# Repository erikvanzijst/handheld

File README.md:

# 8-bit handheld multiplayer gaming device

An Open Source Hardware custom designed handheld gaming device.

* powered by an 8-bit AVR XMEGA microcontroller
* ultra low-res 24x16 monochrome display made of discrete LEDS
* authentic 8-bit retro sound and music
* EEPROM-based hiscores
* multiplayer over bidirectional infrared communication
* battery or USB powered

Project write-up at: https://medium.com/@erikvanzijst/diy-8-bit-handheld-multiplayer-gaming-device-cc30baae7372

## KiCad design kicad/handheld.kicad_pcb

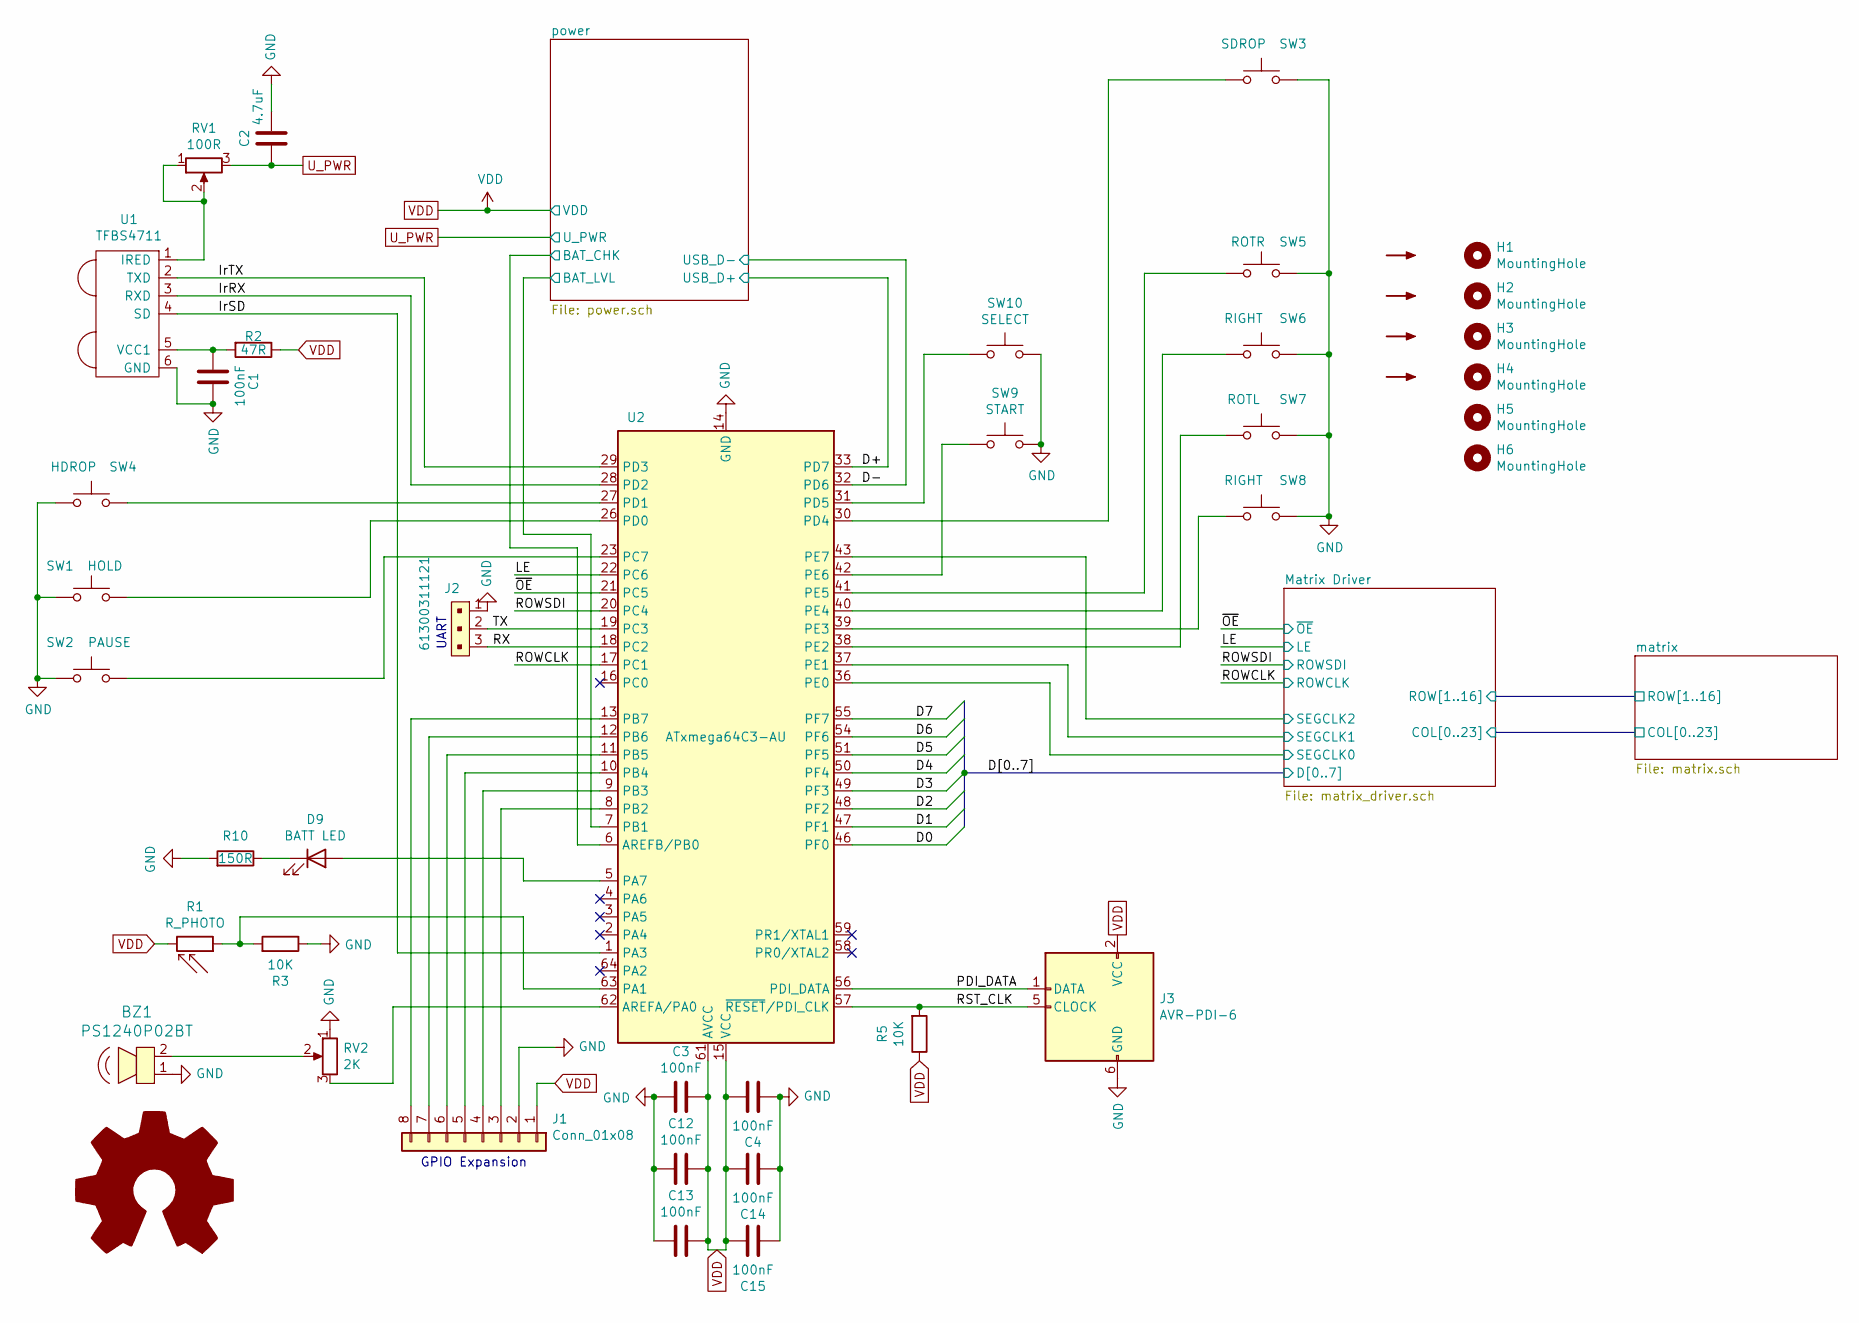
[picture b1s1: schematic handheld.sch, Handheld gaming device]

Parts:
BZ1: PS1240P02BT; Piezo_Transducer_THT_PS1240P02BT; MPN PS1240P02BT; Digi-Key_PN 445-2525-1-ND
C1, C3, C4, C12, C13, C14, C15: 100nF; C_0805_2012Metric_Pad1.15x1.40mm_HandSolder
C2: 4.7uF; C_0805_2012Metric_Pad1.15x1.40mm_HandSolder
D9: BATT LED; LED_D3.0mm
H1, H2, H3, H4, H5, H6: MountingHole; MountingHole_3.2mm_M3
J1: Conn_01x08; PinSocket_1x08_P2.54mm_Horizontal
J2: 61300311121; PinSocket_1x03_P2.54mm_Horizontal; MPN 61300311121; Digi-Key_PN 732-5316-ND
J3: AVR-PDI-6; AVR_PDI_Header_2x03_P2.54mm_Vertical
R1: R_PHOTO; R_LDR_5.1x4.3mm_P3.4mm_Vertical
R2: 47R; R_0805_2012Metric_Pad1.15x1.40mm_HandSolder
R3, R5: 10K; R_0805_2012Metric_Pad1.15x1.40mm_HandSolder
R10: 150R; R_0805_2012Metric_Pad1.15x1.40mm_HandSolder
RV1: 100R; Potentiometer_Bourns_TC33X_Vertical
RV2: 2K; Potentiometer_Bourns_TC33X_Vertical
SW1: HOLD; SW_PUSH-12mm
SW2: PAUSE; SW_PUSH-12mm
SW3: SDROP; SW_PUSH-12mm
SW4: HDROP; SW_PUSH-12mm
SW5: ROTR; SW_PUSH-12mm
SW6, SW8: RIGHT; SW_PUSH-12mm
SW7: ROTL; SW_PUSH-12mm
SW9: START; SW_PUSH_6mm
SW10: SELECT; SW_PUSH_6mm
U1: TFBS4711; TFBS4711-IrDA
U2: ATxmega64C3-AU; TQFP-64_14x14mm_P0.8mm

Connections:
/D0: U2.46 (PF0); also elsewhere on the board
/D1: U2.47 (PF1); also elsewhere on the board
/D2: U2.48 (PF2); also elsewhere on the board
/D3: U2.49 (PF3); also elsewhere on the board
/D4: U2.50 (PF4); also elsewhere on the board
/D5: U2.51 (PF5); also elsewhere on the board
/D6: U2.54 (PF6); also elsewhere on the board
/D7: U2.55 (PF7); also elsewhere on the board
/D+: U2.33 (PD7); also elsewhere on the board
/D-: U2.32 (PD6); also elsewhere on the board
/IrRX: U1.3 (RXD), U2.28 (PD2)
/IrSD: U1.4 (SD), U2.1 (PA3)
/IrTX: U1.2 (TXD), U2.29 (PD3)
/LE: U2.22 (PC6); also elsewhere on the board
/Matrix Driver/SEGCLK0: U2.36 (PE0); also elsewhere on the board
/Matrix Driver/SEGCLK1: U2.37 (PE1); also elsewhere on the board
/Matrix Driver/SEGCLK2: U2.43 (PE7); also elsewhere on the board
/PDI_DATA: J3.1 (DATA), U2.56 (PDI_DATA)
/ROWCLK: U2.17 (PC1); also elsewhere on the board
/ROWSDI: U2.20 (PC4); also elsewhere on the board
/RST_CLK: J3.5 (CLOCK), R5.2, U2.57 (~RESET~/PDI_CLK)
/RX: J2.3, U2.18 (PC2)
/TX: J2.2, U2.19 (PC3)
/power/BAT_CHK: U2.6 (AREFB/PB0); also elsewhere on the board
/power/BAT_LVL: U2.7 (PB1); also elsewhere on the board
/~OE: U2.21 (PC5); also elsewhere on the board
GND: BZ1.1, C1.1, C2.2, C3.2, C4.2, C12.2, C13.2, C14.2, C15.2, J1.2, J2.1, J3.6 (GND), R3.1, R10.2, RV2.1, SW1.1, SW2.1, SW3.1, SW4.2, SW5.1, SW6.1, SW7.1, SW8.1, SW9.2, SW10.2, U1.6 (GND), U2.14 (GND), U2.24 (GND), U2.34 (GND), U2.44 (GND), U2.52 (GND), U2.60 (GND); also elsewhere on the board
unnamed: BZ1.2, RV2.2
unnamed: C1.2, R2.2, U1.5 (VCC1)
unnamed: D9.1 (K), R10.1
unnamed: D9.2 (A), U2.5 (PA7)
unnamed: J1.3, U2.8 (PB2)
unnamed: J1.4, U2.9 (PB3)
unnamed: J1.5, U2.10 (PB4)
unnamed: J1.6, U2.11 (PB5)
unnamed: J1.7, U2.12 (PB6)
unnamed: J1.8, U2.13 (PB7)
unnamed: R1.1, R3.2, U2.63 (PA1)
unnamed: RV1.1, RV1.2, U1.1 (IRED)
unnamed: RV2.3, U2.62 (AREFA/PA0)
unnamed: SW1.2, U2.26 (PD0)
unnamed: SW2.2, U2.23 (PC7)
unnamed: SW3.2, U2.30 (PD4)
unnamed: SW4.1, U2.27 (PD1)
unnamed: SW5.2, U2.41 (PE5)
unnamed: SW6.2, U2.40 (PE4)
unnamed: SW7.2, U2.38 (PE2)
unnamed: SW8.2, U2.39 (PE3)
unnamed: SW9.1, U2.42 (PE6)
unnamed: SW10.1, U2.31 (PD5)
U_PWR: C2.1, RV1.3; also elsewhere on the board
VDD: C3.1, C4.1, C12.1, C13.1, C14.1, C15.1, J1.1, J3.2 (VCC), R1.2, R2.1, R5.1, U2.15 (VCC), U2.25 (VCC), U2.35 (VCC), U2.45 (VCC), U2.53 (VCC), U2.61 (AVCC); also elsewhere on the board

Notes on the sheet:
UART
GPIO Expansion

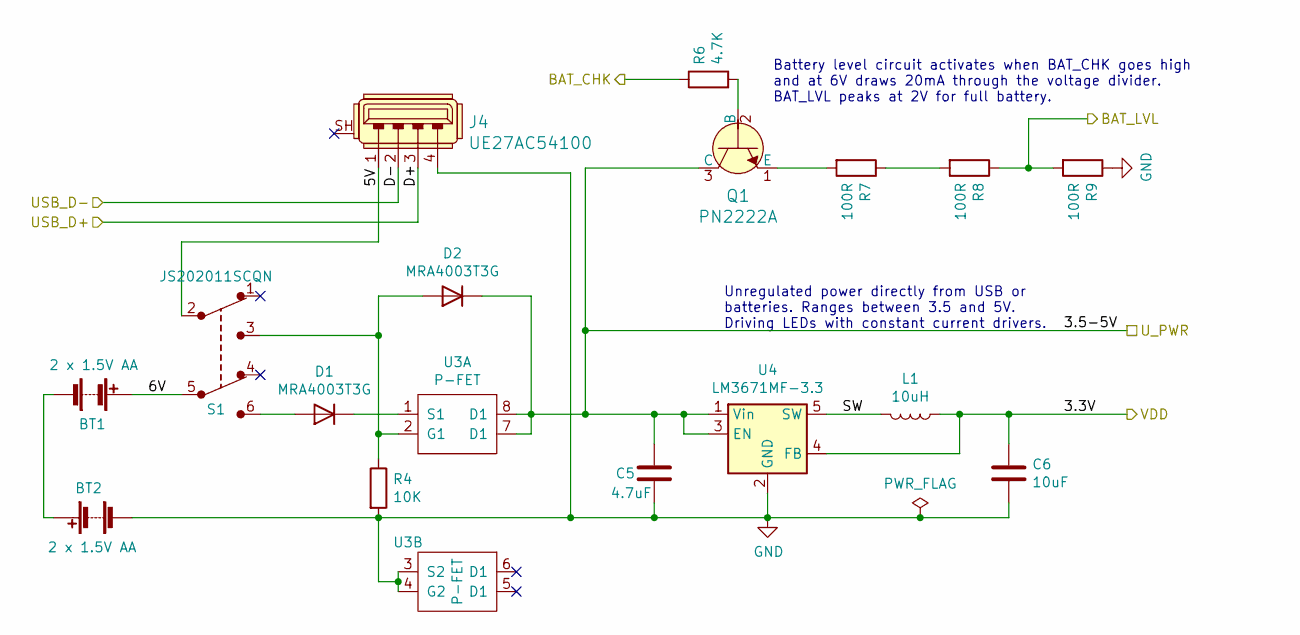
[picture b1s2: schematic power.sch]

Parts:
BT1, BT2: 2 x 1.5V AA; BatteryHolder_MPD_BC12AAPC_2xAA
C5: 4.7uF; C_0805_2012Metric_Pad1.15x1.40mm_HandSolder
C6: 10uF; C_0805_2012Metric_Pad1.15x1.40mm_HandSolder
D1, D2: MRA4003T3G; D_SMA
J4: UE27AC54100; USB_A_Female_UE27AC54100; MPN UE27AC54100; Digi-Key_PN UE27AC54100-ND
L1: 10uH; CDRH5D18NP
Q1: PN2222A; TO-92_Inline_W4.0mm_Horizontal_FlatSideDown; MPN PN2222A; Digi-Key_PN PN2222ACS-ND
R4: 10K; R_0805_2012Metric_Pad1.15x1.40mm_HandSolder
R6: 4.7K; R_0805_2012Metric_Pad1.15x1.40mm_HandSolder
R7, R8, R9: 100R; R_0805_2012Metric_Pad1.15x1.40mm_HandSolder
S1: JS202011SCQN; SW_CuK_JS202011AQN_DPDT_Angled; MPN JS202011SCQN; Digi-Key_PN 401-2002-1-ND
U3: P-FET; SOIC-8_3.9x4.9mm_P1.27mm
U4: LM3671MF-3.3; TSOT-23-5

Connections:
/D+: J4.3; also elsewhere on the board
/D-: J4.2; also elsewhere on the board
/power/5V: J4.1, S1.2
/power/6V: BT1.1 (+), S1.5
/power/BAT_CHK: R6.1; also elsewhere on the board
/power/BAT_LVL: R8.1, R9.2; also elsewhere on the board
/power/SW: L1.2, U4.5 (SW)
GND: BT2.2 (-), C5.2, C6.2, J4.4, R4.2, R9.1, U3.3 (S2), U3.4 (G2), U4.2 (GND); also elsewhere on the board
unnamed: BT1.2 (-), BT2.1 (+)
unnamed: D1.1 (K), U3.1 (S1)
unnamed: D1.2 (A), S1.6
unnamed: D2.2 (A), R4.1, S1.3, U3.2 (G1)
unnamed: Q1.1 (E), R7.2
unnamed: Q1.2 (B), R6.2
unnamed: R7.1, R8.2
U_PWR: C5.1, D2.1 (K), Q1.3 (C), U3.7 (D1), U3.8 (D1), U4.1 (Vin), U4.3 (EN); also elsewhere on the board
VDD: C6.1, L1.1, U4.4 (FB); also elsewhere on the board

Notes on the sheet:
Unregulated power directly from USB or batteries. Ranges between 3.5 and 5V. Driving LEDs with constant current drivers.
Battery level circuit activates when BAT_CHK goes high and at 6V draws 20mA through the voltage divider. BAT_LVL peaks at 2V for full battery.

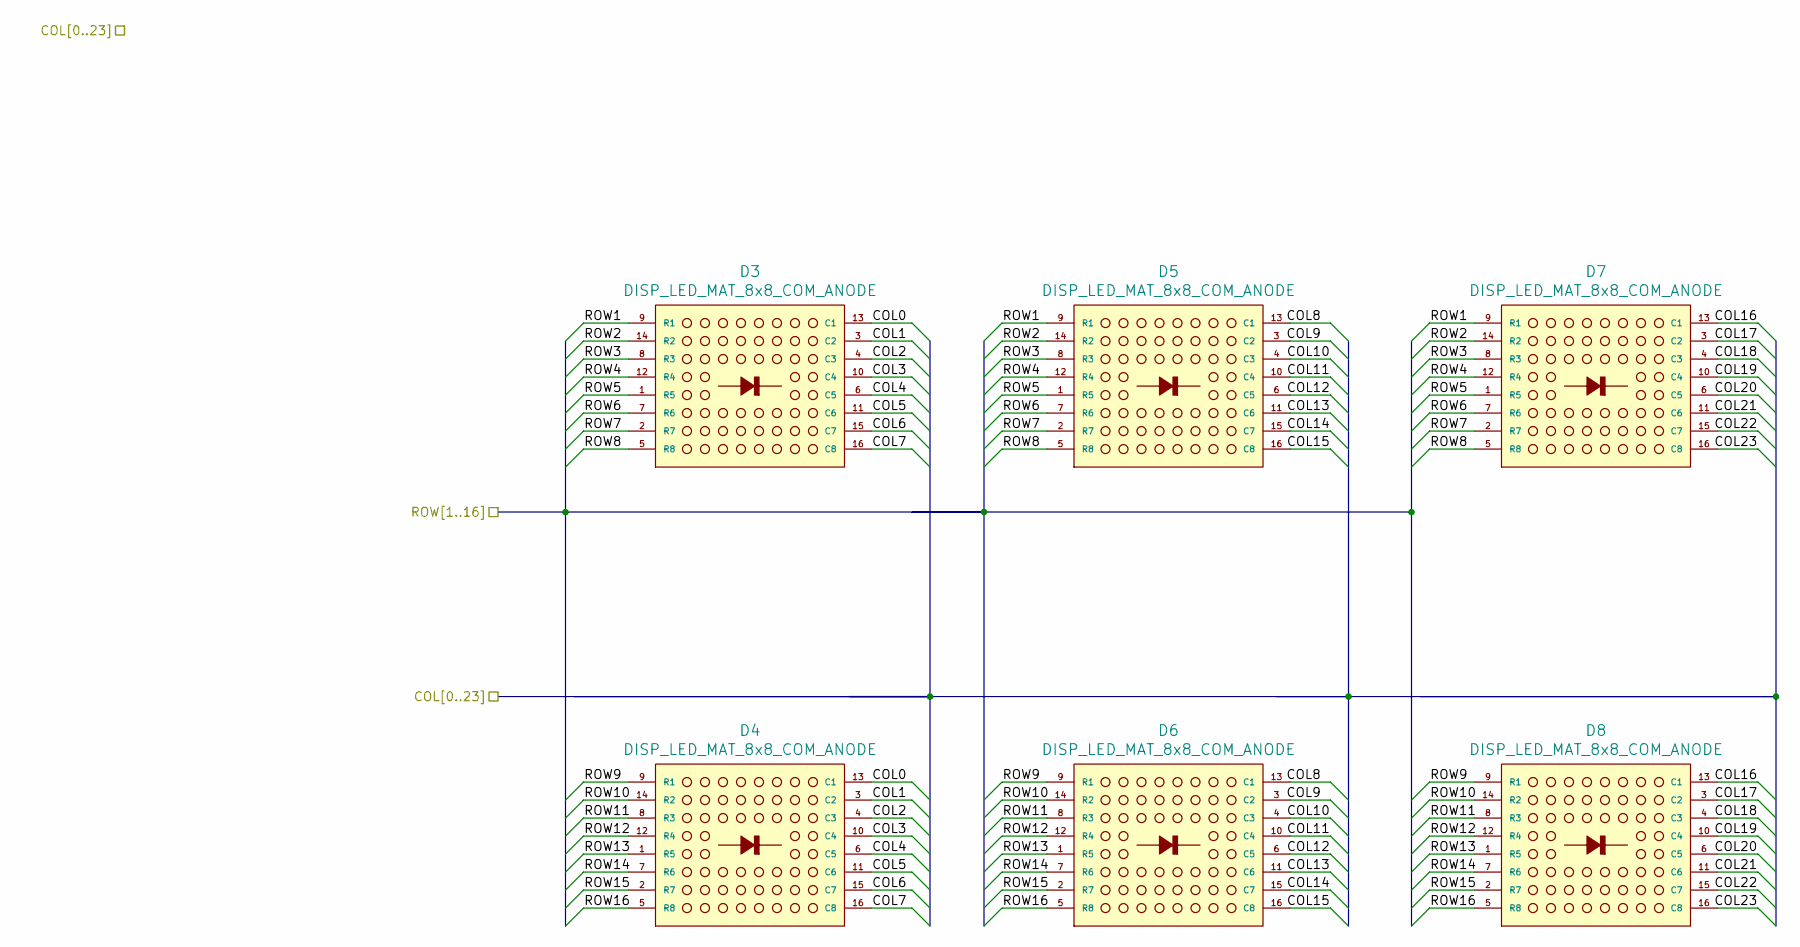
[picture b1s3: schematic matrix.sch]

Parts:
D3, D4, D5, D6, D7, D8: DISP_LED_MAT_8x8_COM_ANODE; LED_8x8_3MM_38x38MM

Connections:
/Matrix Driver/COL0: D3.13 (C1), D4.13 (C1); also elsewhere on the board
/Matrix Driver/COL1: D3.3 (C2), D4.3 (C2); also elsewhere on the board
/Matrix Driver/COL2: D3.4 (C3), D4.4 (C3); also elsewhere on the board
/Matrix Driver/COL3: D3.10 (C4), D4.10 (C4); also elsewhere on the board
/Matrix Driver/COL4: D3.6 (C5), D4.6 (C5); also elsewhere on the board
/Matrix Driver/COL5: D3.11 (C6), D4.11 (C6); also elsewhere on the board
/Matrix Driver/COL6: D3.15 (C7), D4.15 (C7); also elsewhere on the board
/Matrix Driver/COL7: D3.16 (C8), D4.16 (C8); also elsewhere on the board
/Matrix Driver/COL8: D5.13 (C1), D6.13 (C1); also elsewhere on the board
/Matrix Driver/COL9: D5.3 (C2), D6.3 (C2); also elsewhere on the board
/Matrix Driver/COL10: D5.4 (C3), D6.4 (C3); also elsewhere on the board
/Matrix Driver/COL11: D5.10 (C4), D6.10 (C4); also elsewhere on the board
/Matrix Driver/COL12: D5.6 (C5), D6.6 (C5); also elsewhere on the board
/Matrix Driver/COL13: D5.11 (C6), D6.11 (C6); also elsewhere on the board
/Matrix Driver/COL14: D5.15 (C7), D6.15 (C7); also elsewhere on the board
/Matrix Driver/COL15: D5.16 (C8), D6.16 (C8); also elsewhere on the board
/Matrix Driver/COL16: D7.13 (C1), D8.13 (C1); also elsewhere on the board
/Matrix Driver/COL17: D7.3 (C2), D8.3 (C2); also elsewhere on the board
/Matrix Driver/COL18: D7.4 (C3), D8.4 (C3); also elsewhere on the board
/Matrix Driver/COL19: D7.10 (C4), D8.10 (C4); also elsewhere on the board
/Matrix Driver/COL20: D7.6 (C5), D8.6 (C5); also elsewhere on the board
/Matrix Driver/COL21: D7.11 (C6), D8.11 (C6); also elsewhere on the board
/Matrix Driver/COL22: D7.15 (C7), D8.15 (C7); also elsewhere on the board
/Matrix Driver/COL23: D7.16 (C8), D8.16 (C8); also elsewhere on the board
/Matrix Driver/ROW1: D3.9 (R1), D5.9 (R1), D7.9 (R1); also elsewhere on the board
/Matrix Driver/ROW2: D3.14 (R2), D5.14 (R2), D7.14 (R2); also elsewhere on the board
/Matrix Driver/ROW3: D3.8 (R3), D5.8 (R3), D7.8 (R3); also elsewhere on the board
/Matrix Driver/ROW4: D3.12 (R4), D5.12 (R4), D7.12 (R4); also elsewhere on the board
/Matrix Driver/ROW5: D3.1 (R5), D5.1 (R5), D7.1 (R5); also elsewhere on the board
/Matrix Driver/ROW6: D3.7 (R6), D5.7 (R6), D7.7 (R6); also elsewhere on the board
/Matrix Driver/ROW7: D3.2 (R7), D5.2 (R7), D7.2 (R7); also elsewhere on the board
/Matrix Driver/ROW8: D3.5 (R8), D5.5 (R8), D7.5 (R8); also elsewhere on the board
/Matrix Driver/ROW9: D4.9 (R1), D6.9 (R1), D8.9 (R1); also elsewhere on the board
/Matrix Driver/ROW10: D4.14 (R2), D6.14 (R2), D8.14 (R2); also elsewhere on the board
/Matrix Driver/ROW11: D4.8 (R3), D6.8 (R3), D8.8 (R3); also elsewhere on the board
/Matrix Driver/ROW12: D4.12 (R4), D6.12 (R4), D8.12 (R4); also elsewhere on the board
/Matrix Driver/ROW13: D4.1 (R5), D6.1 (R5), D8.1 (R5); also elsewhere on the board
/Matrix Driver/ROW14: D4.7 (R6), D6.7 (R6), D8.7 (R6); also elsewhere on the board
/Matrix Driver/ROW15: D4.2 (R7), D6.2 (R7), D8.2 (R7); also elsewhere on the board
/Matrix Driver/ROW16: D4.5 (R8), D6.5 (R8), D8.5 (R8); also elsewhere on the board

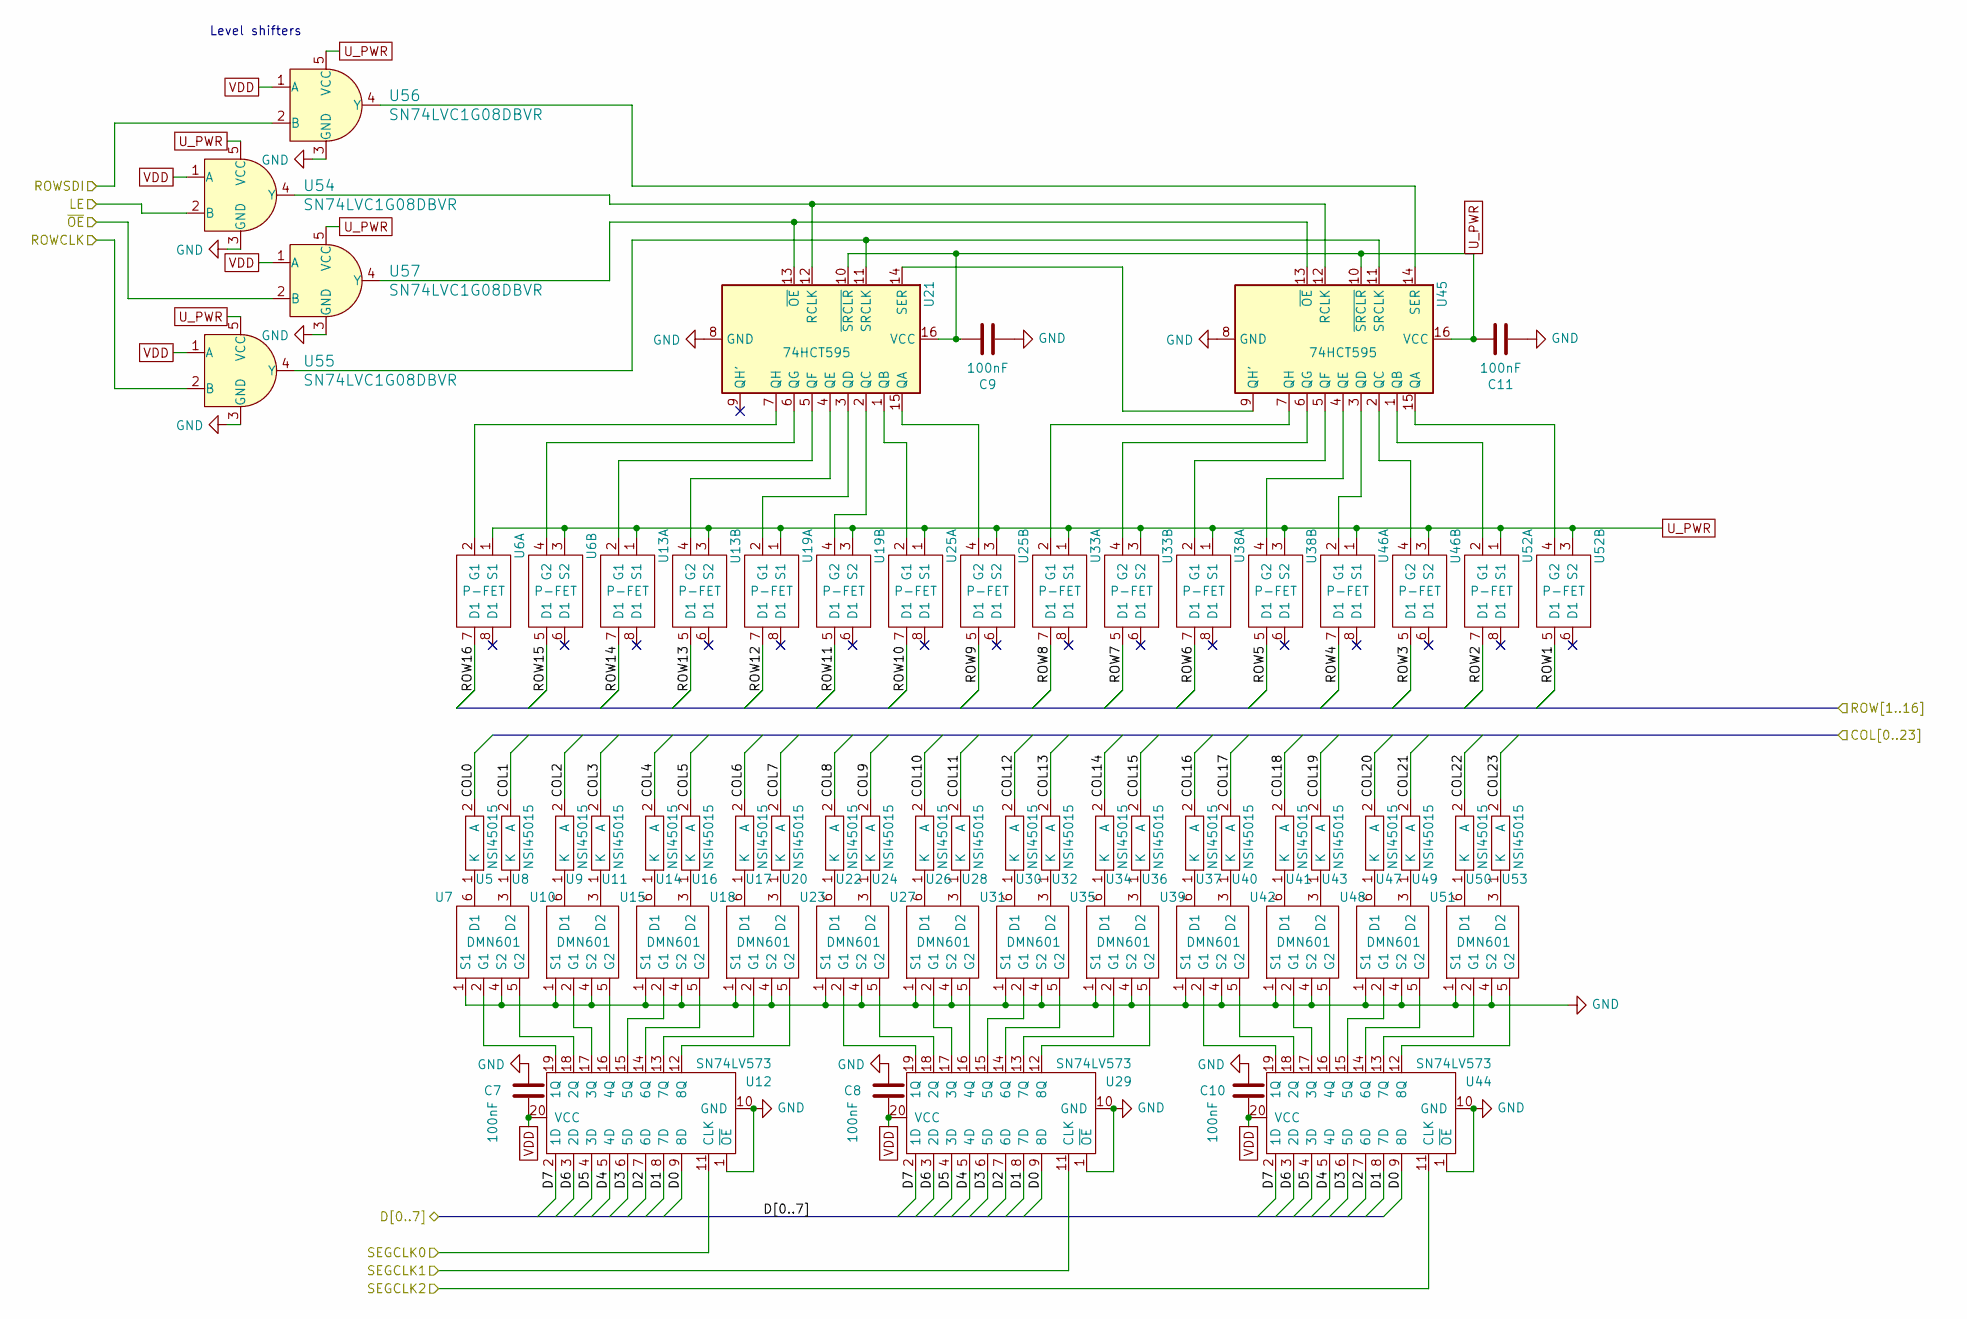
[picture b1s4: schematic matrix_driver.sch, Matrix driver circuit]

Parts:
C7, C8, C9, C10, C11: 100nF; C_0805_2012Metric_Pad1.15x1.40mm_HandSolder
U5, U8, U9, U11, U14, U16, U17, U20, U22, U24, U26, U28, U30, U32, U34, U36, U37, U40, U41, U43, U47, U49, U50, U53: NSI45015; D_SOD-123
U6, U13, U19, U25, U33, U38, U46, U52: P-FET; SOIC-8_3.9x4.9mm_P1.27mm
U7, U10, U15, U18, U23, U27, U31, U35, U39, U42, U48, U51: DMN601; SOT-23-6_Handsoldering
U12, U29, U44: SN74LV573; SO-20_5.3x12.6mm_P1.27mm
U21, U45: 74HCT595; SOIC-16_3.9x9.9mm_P1.27mm
U54, U55, U56, U57: SN74LVC1G08DBVR; SOT-23-5; MPN SN74LVC1G08DBVR; Digi-Key_PN 296-11601-1-ND

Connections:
/D0: U12.9 (8D), U29.9 (8D), U44.9 (8D); also elsewhere on the board
/D1: U12.8 (7D), U29.8 (7D), U44.8 (7D); also elsewhere on the board
/D2: U12.7 (6D), U29.7 (6D), U44.7 (6D); also elsewhere on the board
/D3: U12.6 (5D), U29.6 (5D), U44.6 (5D); also elsewhere on the board
/D4: U12.5 (4D), U29.5 (4D), U44.5 (4D); also elsewhere on the board
/D5: U12.4 (3D), U29.4 (3D), U44.4 (3D); also elsewhere on the board
/D6: U12.3 (2D), U29.3 (2D), U44.3 (2D); also elsewhere on the board
/D7: U12.2 (1D), U29.2 (1D), U44.2 (1D); also elsewhere on the board
/LE: U54.2 (B); also elsewhere on the board
/Matrix Driver/COL0: U5.2 (A); also elsewhere on the board
/Matrix Driver/COL1: U8.2 (A); also elsewhere on the board
/Matrix Driver/COL2: U9.2 (A); also elsewhere on the board
/Matrix Driver/COL3: U11.2 (A); also elsewhere on the board
/Matrix Driver/COL4: U14.2 (A); also elsewhere on the board
/Matrix Driver/COL5: U16.2 (A); also elsewhere on the board
/Matrix Driver/COL6: U17.2 (A); also elsewhere on the board
/Matrix Driver/COL7: U20.2 (A); also elsewhere on the board
/Matrix Driver/COL8: U22.2 (A); also elsewhere on the board
/Matrix Driver/COL9: U24.2 (A); also elsewhere on the board
/Matrix Driver/COL10: U26.2 (A); also elsewhere on the board
/Matrix Driver/COL11: U28.2 (A); also elsewhere on the board
/Matrix Driver/COL12: U30.2 (A); also elsewhere on the board
/Matrix Driver/COL13: U32.2 (A); also elsewhere on the board
/Matrix Driver/COL14: U34.2 (A); also elsewhere on the board
/Matrix Driver/COL15: U36.2 (A); also elsewhere on the board
/Matrix Driver/COL16: U37.2 (A); also elsewhere on the board
/Matrix Driver/COL17: U40.2 (A); also elsewhere on the board
/Matrix Driver/COL18: U41.2 (A); also elsewhere on the board
/Matrix Driver/COL19: U43.2 (A); also elsewhere on the board
/Matrix Driver/COL20: U47.2 (A); also elsewhere on the board
/Matrix Driver/COL21: U49.2 (A); also elsewhere on the board
/Matrix Driver/COL22: U50.2 (A); also elsewhere on the board
/Matrix Driver/COL23: U53.2 (A); also elsewhere on the board
/Matrix Driver/ROW1: U52.5 (D1); also elsewhere on the board
/Matrix Driver/ROW2: U52.7 (D1); also elsewhere on the board
/Matrix Driver/ROW3: U46.5 (D1); also elsewhere on the board
/Matrix Driver/ROW4: U46.7 (D1); also elsewhere on the board
/Matrix Driver/ROW5: U38.5 (D1); also elsewhere on the board
/Matrix Driver/ROW6: U38.7 (D1); also elsewhere on the board
/Matrix Driver/ROW7: U33.5 (D1); also elsewhere on the board
/Matrix Driver/ROW8: U33.7 (D1); also elsewhere on the board
/Matrix Driver/ROW9: U25.5 (D1); also elsewhere on the board
/Matrix Driver/ROW10: U25.7 (D1); also elsewhere on the board
/Matrix Driver/ROW11: U19.5 (D1); also elsewhere on the board
/Matrix Driver/ROW12: U19.7 (D1); also elsewhere on the board
/Matrix Driver/ROW13: U13.5 (D1); also elsewhere on the board
/Matrix Driver/ROW14: U13.7 (D1); also elsewhere on the board
/Matrix Driver/ROW15: U6.5 (D1); also elsewhere on the board
/Matrix Driver/ROW16: U6.7 (D1); also elsewhere on the board
/Matrix Driver/SEGCLK0: U12.11 (CLK); also elsewhere on the board
/Matrix Driver/SEGCLK1: U29.11 (CLK); also elsewhere on the board
/Matrix Driver/SEGCLK2: U44.11 (CLK); also elsewhere on the board
/ROWCLK: U55.2 (B); also elsewhere on the board
/ROWSDI: U56.2 (B); also elsewhere on the board
/~OE: U57.2 (B); also elsewhere on the board
GND: C7.1, C8.1, C9.2, C10.1, C11.2, U7.1 (S1), U7.4 (S2), U10.1 (S1), U10.4 (S2), U12.1 (~OE), U12.10 (GND), U15.1 (S1), U15.4 (S2), U18.1 (S1), U18.4 (S2), U21.8 (GND), U23.1 (S1), U23.4 (S2), U27.1 (S1), U27.4 (S2), U29.1 (~OE), U29.10 (GND), U31.1 (S1), U31.4 (S2), U35.1 (S1), U35.4 (S2), U39.1 (S1), U39.4 (S2), U42.1 (S1), U42.4 (S2), U44.1 (~OE), U44.10 (GND), U45.8 (GND), U48.1 (S1), U48.4 (S2), U51.1 (S1), U51.4 (S2), U54.3 (GND), U55.3 (GND), U56.3 (GND), U57.3 (GND); also elsewhere on the board
unnamed: U5.1 (K), U7.6 (D1)
unnamed: U7.3 (D2), U8.1 (K)
unnamed: U10.2 (G1), U12.17 (3Q)
unnamed: U10.3 (D2), U11.1 (K)
unnamed: U10.5 (G2), U12.16 (4Q)
unnamed: U9.1 (K), U10.6 (D1)
unnamed: U12.12 (8Q), U18.5 (G2)
unnamed: U12.13 (7Q), U18.2 (G1)
unnamed: U12.14 (6Q), U15.5 (G2)
unnamed: U12.15 (5Q), U15.2 (G1)
unnamed: U7.5 (G2), U12.18 (2Q)
unnamed: U7.2 (G1), U12.19 (1Q)
unnamed: U13.2 (G1), U21.5 (QF)
unnamed: U13.4 (G2), U21.4 (QE)
unnamed: U14.1 (K), U15.6 (D1)
unnamed: U15.3 (D2), U16.1 (K)
unnamed: U17.1 (K), U18.6 (D1)
unnamed: U18.3 (D2), U20.1 (K)
unnamed: U19.2 (G1), U21.3 (QD)
unnamed: U19.4 (G2), U21.2 (QC)
unnamed: U21.1 (QB), U25.2 (G1)
unnamed: U6.4 (G2), U21.6 (QG)
unnamed: U6.2 (G1), U21.7 (QH)
unnamed: U21.11 (SRCLK), U45.11 (SRCLK), U55.4 (Y)
unnamed: U21.12 (RCLK), U45.12 (RCLK), U54.4 (Y)
unnamed: U21.13 (~OE), U45.13 (~OE), U57.4 (Y)
unnamed: U21.14 (SER), U45.9 (QH')
unnamed: U21.15 (QA), U25.4 (G2)
unnamed: U22.1 (K), U23.6 (D1)
unnamed: U23.2 (G1), U29.19 (1Q)
unnamed: U23.3 (D2), U24.1 (K)
unnamed: U23.5 (G2), U29.18 (2Q)
unnamed: U26.1 (K), U27.6 (D1)
unnamed: U27.2 (G1), U29.17 (3Q)
unnamed: U27.3 (D2), U28.1 (K)
unnamed: U27.5 (G2), U29.16 (4Q)
unnamed: U29.12 (8Q), U35.5 (G2)
unnamed: U29.13 (7Q), U35.2 (G1)
unnamed: U29.14 (6Q), U31.5 (G2)
unnamed: U29.15 (5Q), U31.2 (G1)
unnamed: U30.1 (K), U31.6 (D1)
unnamed: U31.3 (D2), U32.1 (K)
unnamed: U33.2 (G1), U45.7 (QH)
unnamed: U33.4 (G2), U45.6 (QG)
unnamed: U34.1 (K), U35.6 (D1)
unnamed: U35.3 (D2), U36.1 (K)
unnamed: U37.1 (K), U39.6 (D1)
unnamed: U38.2 (G1), U45.5 (QF)
unnamed: U38.4 (G2), U45.4 (QE)
unnamed: U39.2 (G1), U44.19 (1Q)
unnamed: U39.3 (D2), U40.1 (K)
unnamed: U39.5 (G2), U44.18 (2Q)
unnamed: U41.1 (K), U42.6 (D1)
unnamed: U42.2 (G1), U44.17 (3Q)
unnamed: U42.3 (D2), U43.1 (K)
unnamed: U42.5 (G2), U44.16 (4Q)
unnamed: U44.12 (8Q), U51.5 (G2)
unnamed: U44.13 (7Q), U51.2 (G1)
unnamed: U44.14 (6Q), U48.5 (G2)
unnamed: U44.15 (5Q), U48.2 (G1)
unnamed: U45.1 (QB), U52.2 (G1)
unnamed: U45.2 (QC), U46.4 (G2)
unnamed: U45.3 (QD), U46.2 (G1)
unnamed: U45.14 (SER), U56.4 (Y)
unnamed: U45.15 (QA), U52.4 (G2)
unnamed: U47.1 (K), U48.6 (D1)
unnamed: U48.3 (D2), U49.1 (K)
unnamed: U50.1 (K), U51.6 (D1)
unnamed: U51.3 (D2), U53.1 (K)
U_PWR: C9.1, C11.1, U6.1 (S1), U6.3 (S2), U13.1 (S1), U13.3 (S2), U19.1 (S1), U19.3 (S2), U21.10 (~SRCLR), U21.16 (VCC), U25.1 (S1), U25.3 (S2), U33.1 (S1), U33.3 (S2), U38.1 (S1), U38.3 (S2), U45.10 (~SRCLR), U45.16 (VCC), U46.1 (S1), U46.3 (S2), U52.1 (S1), U52.3 (S2), U54.5 (VCC), U55.5 (VCC), U56.5 (VCC), U57.5 (VCC); also elsewhere on the board
VDD: C7.2, C8.2, C10.2, U12.20 (VCC), U29.20 (VCC), U44.20 (VCC), U54.1 (A), U55.1 (A), U56.1 (A), U57.1 (A); also elsewhere on the board

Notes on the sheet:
Level shifters

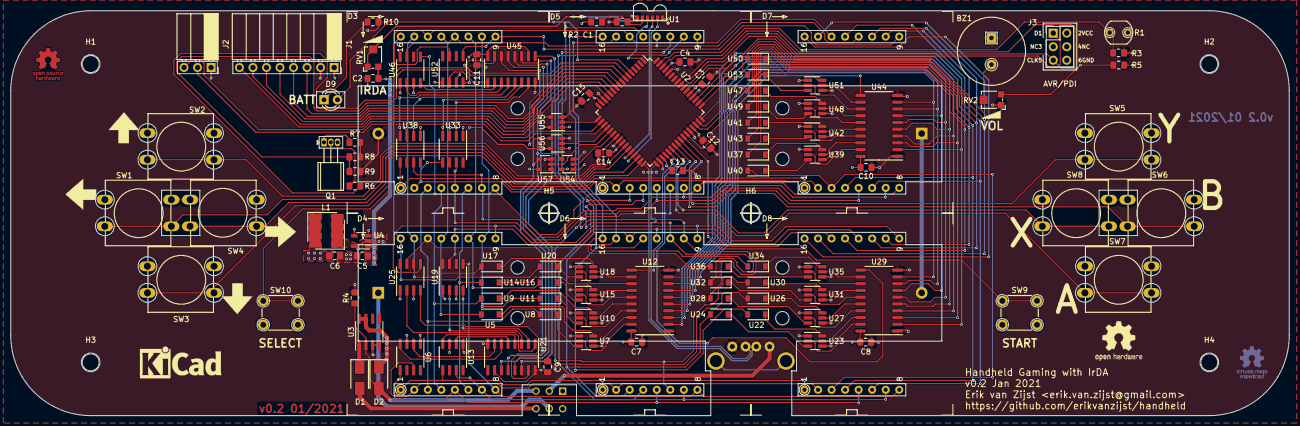
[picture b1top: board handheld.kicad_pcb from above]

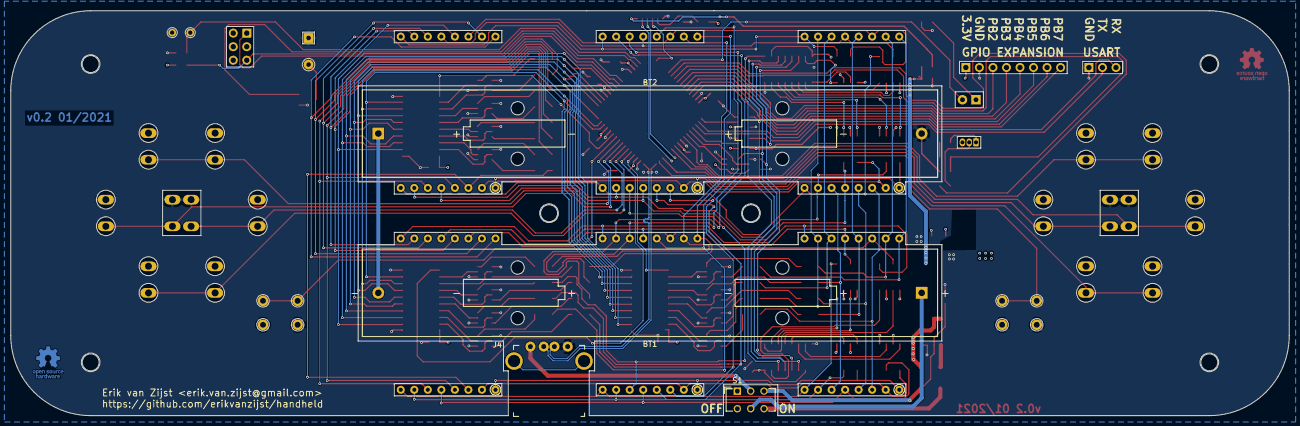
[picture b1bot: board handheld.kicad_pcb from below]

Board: 4 copper layers, 239.9 x 75.9 mm, 119 parts (4 on the bottom side), 171 nets.

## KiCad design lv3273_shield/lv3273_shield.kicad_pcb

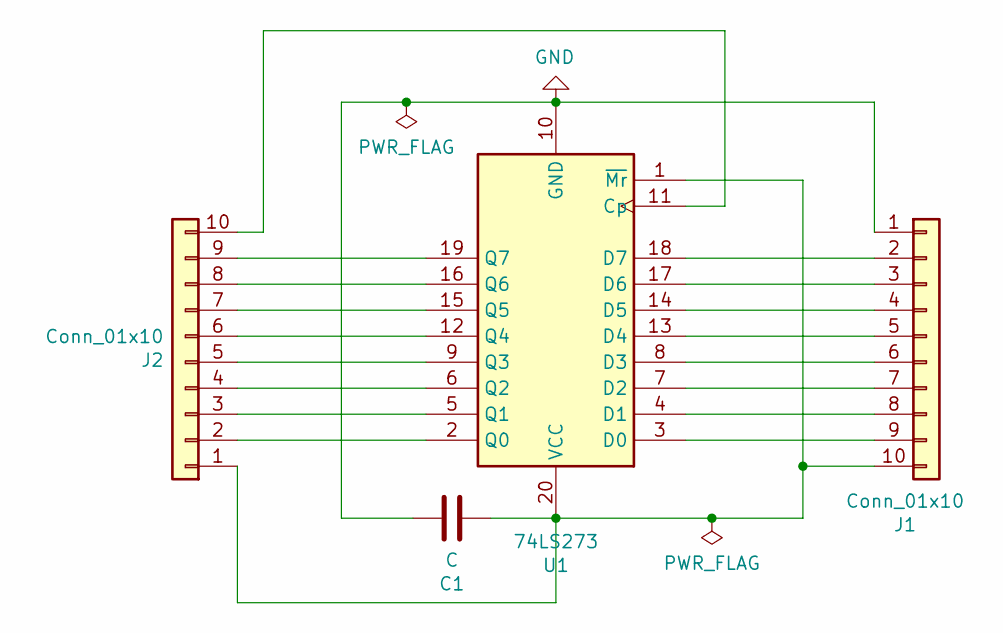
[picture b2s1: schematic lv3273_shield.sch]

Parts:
C1: C; C_0805_2012Metric
J1, J2: Conn_01x10; PinHeader_1x10_P1.00mm_Vertical
U1: 74LS273; SO-20_5.3x12.6mm_P1.27mm

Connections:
GND: C1.1, J1.1, U1.10 (GND)
unnamed: C1.2, J1.10, J2.1, U1.1 (~Mr), U1.20 (VCC)
unnamed: J1.2, U1.18 (D7)
unnamed: J1.3, U1.17 (D6)
unnamed: J1.4, U1.14 (D5)
unnamed: J1.5, U1.13 (D4)
unnamed: J1.6, U1.8 (D3)
unnamed: J1.7, U1.7 (D2)
unnamed: J1.8, U1.4 (D1)
unnamed: J1.9, U1.3 (D0)
unnamed: J2.2, U1.2 (Q0)
unnamed: J2.3, U1.5 (Q1)
unnamed: J2.4, U1.6 (Q2)
unnamed: J2.5, U1.9 (Q3)
unnamed: J2.6, U1.12 (Q4)
unnamed: J2.7, U1.15 (Q5)
unnamed: J2.8, U1.16 (Q6)
unnamed: J2.9, U1.19 (Q7)
unnamed: J2.10, U1.11 (Cp)

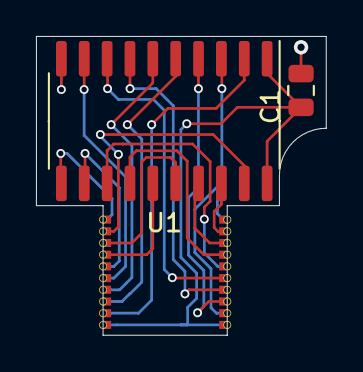
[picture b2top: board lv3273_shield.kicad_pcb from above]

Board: 2 copper layers, 16.1 x 16.6 mm, 4 parts (0 on the bottom side), 19 nets.

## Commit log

2020-07-25 Initial commit
    Carrying over the custom matrix display design as starting point.
2020-07-26 Renamed KiCad project
2020-07-26 Add datasheets
2020-07-27 Working on schematic
2020-07-27 Add datasheet for 74HC273 8-bit register
2020-08-03 Add datasheets for buck converter and trimmer pot
2020-08-03 Add power sheet
2020-08-23 Move displays to separate sheet
2020-08-24 Clean up DRC errors and buses
2020-10-12 Change column control to 8 bit bus
2020-10-12 Finishes matrix driver circuit
2020-10-13 Switches to ATXMEGA64C3 for USB
2020-10-13 Adds IrDA transceiver
2020-10-13 Adds footprint for IrDA module
2020-10-13 Adds power switch
2020-10-13 Adds piezo buzzer
2020-10-14 Adds GPIO expansion port
2020-10-14 Adds AA battery holders
2020-10-15 Adds AVR/PDI header footprint
2020-10-15 Adds inductor datasheet
2020-10-15 Adds inductor footprint
2020-10-15 Fixes footprints
2020-10-16 Switches battery holders and adds switch footprint
2020-10-16 Adds board outline
2020-10-17 Starts matrix driver component layout
2020-10-17 Adds column drivers
2020-10-18 First stab at constant current drivers
2020-10-18 Adds more constant current drivers
2020-10-18 Adds more column circuitry
2020-10-19 Wires up USB and buttons
2020-11-22 Added power plane and reassigned pinout
2020-11-23 Wired up buzzer and LDR
2020-11-23 Places rectifiers
2020-11-27 Added power net and buck converter
    Also wired up Ir transceiver.
2020-11-27 Added GPIO expansion header
2020-11-27 Add ATMEGA schematic checklist doc
2020-11-28 Decouple microcontroller
2020-11-28 Add 3D models
2020-11-29 Adds SELECT button
2020-11-29 Adds Bourns TC33X 3D model
2020-11-30 Adding level shifters
2020-12-13 Wired up battery level check
2020-12-13 Added mounting holes
2020-12-14 Add silkscreen art and version
2020-12-14 Add logos
2020-12-21 Fix register footprints and add batt indicator
2020-12-21 Switched to registers with clear
    Also added the mountng holes as annotated symbols with footprints.
2020-12-22 Add silkscreen art
2020-12-22 Reduce pad with for SSOP-20 footprint
    This ensures there's solder mask between the pads.
2020-12-22 Completed v0.1
2020-12-23 Fix UPWR/GND short circuit on front copper
    Caught a zone priority error that caused power and ground pours
    to overlap and short circuit.
    Unfortunately the board is already being fabricated and so this
    will have to be bodged on v0.1.
2020-12-29 Fix solder mask margins and named programming nets
2021-01-17 Adds initial firmware
2021-01-17 Add pin assignments
2021-01-17 Disable display bus due to footprint error
    The footprint of the 74LV273 octal flip-flop is wrong and doesn't
    match that of the actual chip. As a result, the flip-flops cannot
    be used and the bus must be set to high impedance for now.
    Next step might be an adaptor board that can be soldered on top of
    the footprint.
2021-01-17 Document power/gnd plane short circuit bug
2021-01-17 Disconnect USB shield from ground plane
    Also Fixed obscured refdes indicators.
2021-01-17 Draw outlines for 74lv273 castellated shield
2021-01-18 Adds errata shield PCB for messed up SSOP-20 pinout
2021-01-18 Remove shield measurements
2021-01-18 Swith back to 74LV573 flip-flop
    This changes switches back to the original 74LV573 octal flip-flop
    instead of the 273. This due to the pinout difference and the fact
    that the board already followed the pinout of th 573.
    Package is still SSOP-20.
2021-01-19 Switched back to SOIC-20 package for the 74LV573s
    Because they're easier to solder and we've got enough space.
2021-01-24 Add a Dockerfile with the avr toolchain
2021-01-24 Test routines for display panel
2021-01-24 Testing column circuitry
2021-01-25 Add XMega256C manual
2021-01-25 Adding timer and interrupt vector
2021-01-31 Enabling the screen redraw interrupt vector
2021-01-31 Bounce a ball around the screen
2021-01-31 Add USART on external board header
    Prints out the location of the bouncy ball on the UART in real time.
2021-01-31 Add 5x5 font
2021-01-31 Implement ASCII text scrolling
2021-01-31 Add a millis() function to return millis since boot
2021-02-01 Add real time clock
2021-02-01 Add button polling and debouncing
2021-02-01 Add scaffolding for Tetris
2021-02-02 Butchered board into mounting plate with THT holes
2021-02-02 Butcher edge cuts into bottom mounting plate
2021-02-03 Add text and attribution to mounting board
2021-02-03 Add button definitions
    Also set random seed from human button press delay.
2021-02-08 Implement most of tetris
2021-02-08 Add EEPROM-backed hiscore
2021-02-09 Add preview for next tetromino
2021-02-11 Add more tetromino previews
2021-02-13 Don't merge the brick while the player is still moving
2021-02-13 License firmware under MIT
2021-02-15 Add sound and melody driver
    Also adds the Tetris and Super Mario melodies.
2021-02-15 Add game over tune when you die
2021-02-15 Select button mutes sound
2021-02-15 Add attribution for melodies
2021-02-15 Add a hold section
    Pressing UP now switches the current tetromino with the one in the
    hold section on the top left. Only one swap is allowed per brick.
2021-02-28 First attempt at UART over IRCOMM and IrDA
2021-03-01 Add IrDA specification documents
2021-03-22 Added logic analyzer images of Ir UART traffic
2021-03-29 First stab at packetization over IrDA.
2022-02-07 Add glyphs to the font.
2022-03-06 Add alarm function
    To be used in future IrDA wire protocol.
2022-03-09 Initial working IrDA
    This is a rough initial implementation of half-duplex packet-based
    transmission over IrDA.
2022-03-11 Add CRC-16 checksum to packets and apply validation
    This uses the XMega's hardware CRC engine.
2022-03-11 Refactor for 1 and 2 player implementations
2022-03-12 Add initial multiplayer capability
2022-03-12 Add link status logging
2022-03-13 Publish # lines removed in each packet
    This will allow us to add the peer's lines to our board.
2022-03-13 Move completed lines to opponent
2022-03-14 Sync at start and end of game
    Players can now win and lose the game.
2022-03-14 Simplify post-game synchronization code
2022-03-14 Add sounds to multiplayer
    Also sped up set_alarm() by substituting very slow 64 bit integer
    division by bit shift.
2022-03-14 Add media files
2022-03-15 Add victory tune to the post-game screen
    Melody is the flagpole tune from Super Mario.
2022-03-15 Add version and build date to firmare
2022-03-15 Add a second general purpose alarm
2022-03-16 Move irda_write to ISR and scroll end screen
    Now publishing the IrDA packets from the new, second alarm
    interrupt, freeing up the main loop to scroll the text on the end
    screen.
2022-03-16 Pause while disconnected in multiplayer
    Also show a spinner on start game sync.
2022-03-16 Display a spinner when disconnected
2022-03-16 Fixed display corruption in right hand board
2022-03-17 Fix deadlock bug in reconnect logic
    When the connection was lost in one direction and while it's down
    one player dies, then the synchronization would deadlock upon
    reconnection.
2022-03-17 Add GitHub Action CI pipeline for firmware compilation
2022-03-17 Make mcu spec compatible with both gcc-avr 5.4.0 and 9.3.0
2022-03-17 Add Docker compilation instructions
2022-03-17 Add CI status badge to firmware README
2022-03-17 Update firmware README
2022-03-17 Fix compiler warnings
2022-03-21 Fix bug with insertion of penalty lines
2022-03-21 Add USB bootloader
2022-03-21 Release 1.0
2022-03-22 Add MIT license
2022-03-23 Remove leftover debugging
2022-03-24 Add project README
2022-04-22 Add missing through hole
2022-06-01 Add datasheet for level shifter
